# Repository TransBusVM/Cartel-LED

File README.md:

# Cartel-LED

Desarrollo de carteles LED para la empresa TransBus S.R.L.

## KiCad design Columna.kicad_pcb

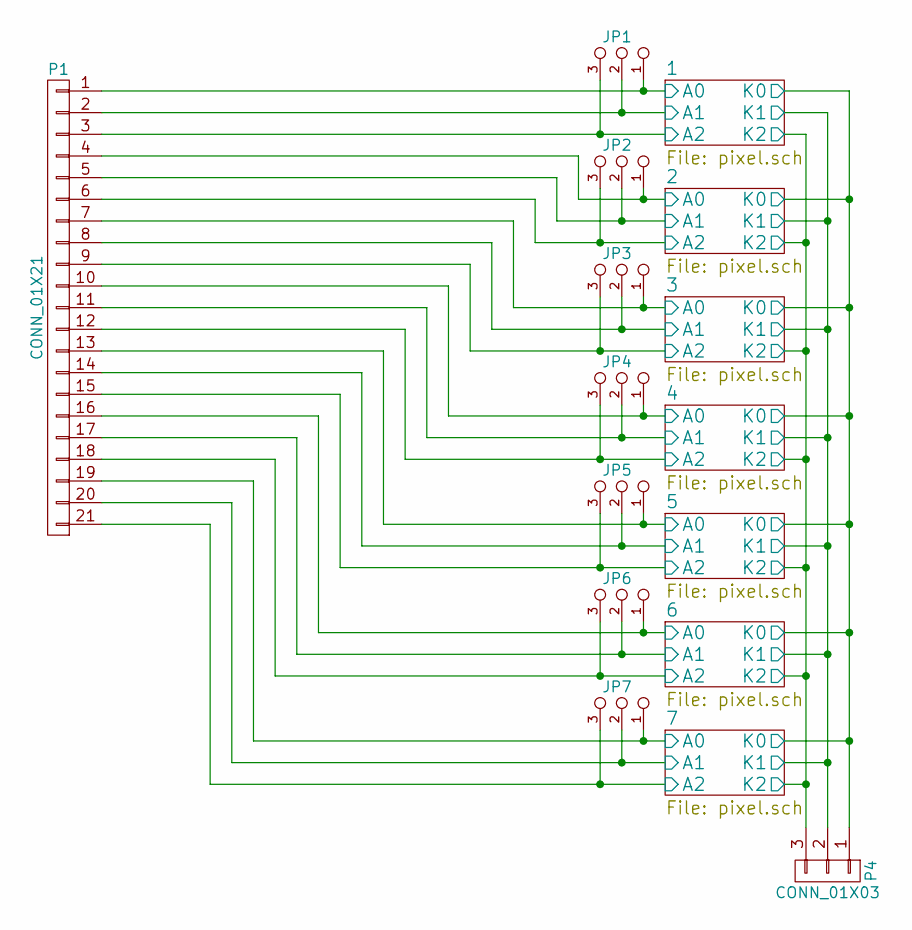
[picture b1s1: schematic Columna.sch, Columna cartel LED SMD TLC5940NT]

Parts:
JP1, JP2, JP3, JP4, JP5, JP6, JP7: JUMPER3_NO; Jumper_3_NO
P1: CONN_01X21; Poste_1x21
P4: CONN_01X03; Poste_1x3

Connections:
/1/A0: JP1.1, P1.1; also elsewhere on the board
/1/A1: JP1.2, P1.2; also elsewhere on the board
/1/A2: JP1.3, P1.3; also elsewhere on the board
/1/K0: P4.1; also elsewhere on the board
/1/K1: P4.2; also elsewhere on the board
/1/K2: P4.3; also elsewhere on the board
/2/A0: JP2.1, P1.4; also elsewhere on the board
/2/A1: JP2.2, P1.5; also elsewhere on the board
/2/A2: JP2.3, P1.6; also elsewhere on the board
/3/A0: JP3.1, P1.7; also elsewhere on the board
/3/A1: JP3.2, P1.8; also elsewhere on the board
/3/A2: JP3.3, P1.9; also elsewhere on the board
/4/A0: JP4.1, P1.10; also elsewhere on the board
/4/A1: JP4.2, P1.11; also elsewhere on the board
/4/A2: JP4.3, P1.12; also elsewhere on the board
/5/A0: JP5.1, P1.13; also elsewhere on the board
/5/A1: JP5.2, P1.14; also elsewhere on the board
/5/A2: JP5.3, P1.15; also elsewhere on the board
/6/A0: JP6.1, P1.16; also elsewhere on the board
/6/A1: JP6.2, P1.17; also elsewhere on the board
/6/A2: JP6.3, P1.18; also elsewhere on the board
/7/A0: JP7.1, P1.19; also elsewhere on the board
/7/A1: JP7.2, P1.20; also elsewhere on the board
/7/A2: JP7.3, P1.21; also elsewhere on the board

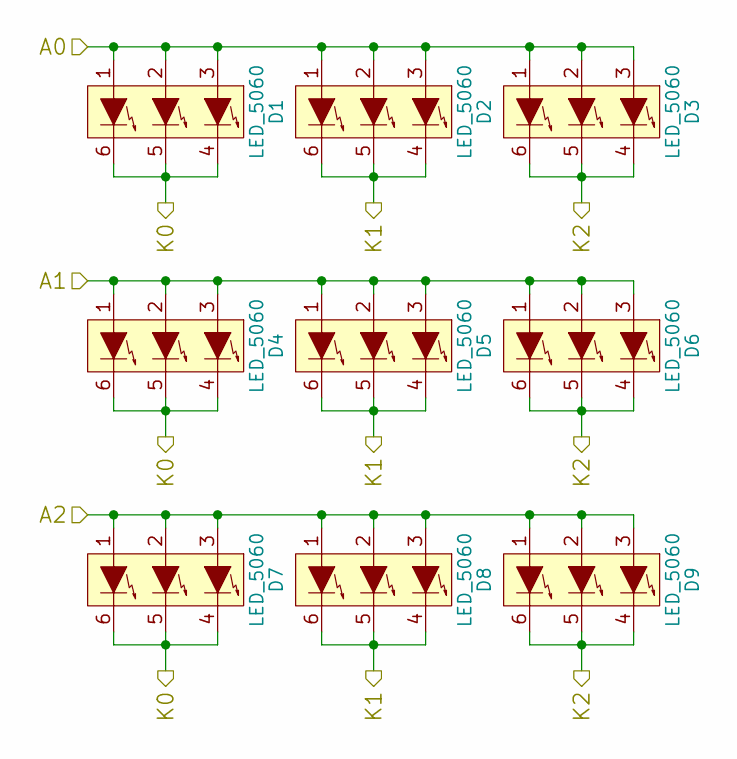
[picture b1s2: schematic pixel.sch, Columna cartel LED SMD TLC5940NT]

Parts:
D1, D2, D3, D4, D5, D6, D7, D8, D9: LED_5060; SMD_5060

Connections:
/1/A0: D1.1, D1.2, D1.3, D2.1, D2.2, D2.3, D3.1, D3.2, D3.3; also elsewhere on the board
/1/A1: D4.1, D4.2, D4.3, D5.1, D5.2, D5.3, D6.1, D6.2, D6.3; also elsewhere on the board
/1/A2: D7.1, D7.2, D7.3, D8.1, D8.2, D8.3, D9.1, D9.2, D9.3; also elsewhere on the board
/1/K0: D1.4, D1.5, D1.6, D4.4, D4.5, D4.6, D7.4, D7.5, D7.6; also elsewhere on the board
/1/K1: D2.4, D2.5, D2.6, D5.4, D5.5, D5.6, D8.4, D8.5, D8.6; also elsewhere on the board
/1/K2: D3.4, D3.5, D3.6, D6.4, D6.5, D6.6, D9.4, D9.5, D9.6; also elsewhere on the board

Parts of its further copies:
D10, D11, D12, D13, D14, D15, D16, D17, D18, D19, D20, D21, D22, D23, D24, D25, D26, D27, D28, D29, D30, D31, D32, D33, D34, D35, D36, D37, D38, D39, D40, D41, D42, D43, D44, D45, D46, D47, D48, D49, D50, D51, D52, D53, D54, D55, D56, D57, D58, D59, D60, D61, D62, D63: LED_5060; SMD_5060

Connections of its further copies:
/1/K0: D10.4, D10.5, D10.6, D13.4, D13.5, D13.6, D16.4, D16.5, D16.6, D19.4, D19.5, D19.6, D22.4, D22.5, D22.6, D25.4, D25.5, D25.6, D28.4, D28.5, D28.6, D31.4, D31.5, D31.6, D34.4, D34.5, D34.6, D37.4, D37.5, D37.6, D40.4, D40.5, D40.6, D43.4, D43.5, D43.6, D46.4, D46.5, D46.6, D49.4, D49.5, D49.6, D52.4, D52.5, D52.6, D55.4, D55.5, D55.6, D58.4, D58.5, D58.6, D61.4, D61.5, D61.6; also elsewhere on the board
/1/K1: D11.4, D11.5, D11.6, D14.4, D14.5, D14.6, D17.4, D17.5, D17.6, D20.4, D20.5, D20.6, D23.4, D23.5, D23.6, D26.4, D26.5, D26.6, D29.4, D29.5, D29.6, D32.4, D32.5, D32.6, D35.4, D35.5, D35.6, D38.4, D38.5, D38.6, D41.4, D41.5, D41.6, D44.4, D44.5, D44.6, D47.4, D47.5, D47.6, D50.4, D50.5, D50.6, D53.4, D53.5, D53.6, D56.4, D56.5, D56.6, D59.4, D59.5, D59.6, D62.4, D62.5, D62.6; also elsewhere on the board
/1/K2: D12.4, D12.5, D12.6, D15.4, D15.5, D15.6, D18.4, D18.5, D18.6, D21.4, D21.5, D21.6, D24.4, D24.5, D24.6, D27.4, D27.5, D27.6, D30.4, D30.5, D30.6, D33.4, D33.5, D33.6, D36.4, D36.5, D36.6, D39.4, D39.5, D39.6, D42.4, D42.5, D42.6, D45.4, D45.5, D45.6, D48.4, D48.5, D48.6, D51.4, D51.5, D51.6, D54.4, D54.5, D54.6, D57.4, D57.5, D57.6, D60.4, D60.5, D60.6, D63.4, D63.5, D63.6; also elsewhere on the board
/2/A0: D10.1, D10.2, D10.3, D11.1, D11.2, D11.3, D12.1, D12.2, D12.3; also elsewhere on the board
/2/A1: D13.1, D13.2, D13.3, D14.1, D14.2, D14.3, D15.1, D15.2, D15.3; also elsewhere on the board
/2/A2: D16.1, D16.2, D16.3, D17.1, D17.2, D17.3, D18.1, D18.2, D18.3; also elsewhere on the board
/3/A0: D19.1, D19.2, D19.3, D20.1, D20.2, D20.3, D21.1, D21.2, D21.3; also elsewhere on the board
/3/A1: D22.1, D22.2, D22.3, D23.1, D23.2, D23.3, D24.1, D24.2, D24.3; also elsewhere on the board
/3/A2: D25.1, D25.2, D25.3, D26.1, D26.2, D26.3, D27.1, D27.2, D27.3; also elsewhere on the board
/4/A0: D28.1, D28.2, D28.3, D29.1, D29.2, D29.3, D30.1, D30.2, D30.3; also elsewhere on the board
/4/A1: D31.1, D31.2, D31.3, D32.1, D32.2, D32.3, D33.1, D33.2, D33.3; also elsewhere on the board
/4/A2: D34.1, D34.2, D34.3, D35.1, D35.2, D35.3, D36.1, D36.2, D36.3; also elsewhere on the board
/5/A0: D37.1, D37.2, D37.3, D38.1, D38.2, D38.3, D39.1, D39.2, D39.3; also elsewhere on the board
/5/A1: D40.1, D40.2, D40.3, D41.1, D41.2, D41.3, D42.1, D42.2, D42.3; also elsewhere on the board
/5/A2: D43.1, D43.2, D43.3, D44.1, D44.2, D44.3, D45.1, D45.2, D45.3; also elsewhere on the board
/6/A0: D46.1, D46.2, D46.3, D47.1, D47.2, D47.3, D48.1, D48.2, D48.3; also elsewhere on the board
/6/A1: D49.1, D49.2, D49.3, D50.1, D50.2, D50.3, D51.1, D51.2, D51.3; also elsewhere on the board
/6/A2: D52.1, D52.2, D52.3, D53.1, D53.2, D53.3, D54.1, D54.2, D54.3; also elsewhere on the board
/7/A0: D55.1, D55.2, D55.3, D56.1, D56.2, D56.3, D57.1, D57.2, D57.3; also elsewhere on the board
/7/A1: D58.1, D58.2, D58.3, D59.1, D59.2, D59.3, D60.1, D60.2, D60.3; also elsewhere on the board
/7/A2: D61.1, D61.2, D61.3, D62.1, D62.2, D62.3, D63.1, D63.2, D63.3; also elsewhere on the board

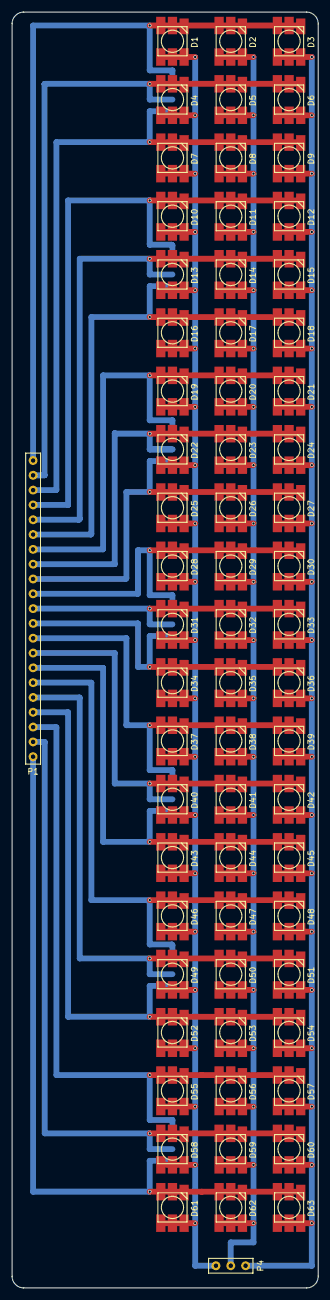
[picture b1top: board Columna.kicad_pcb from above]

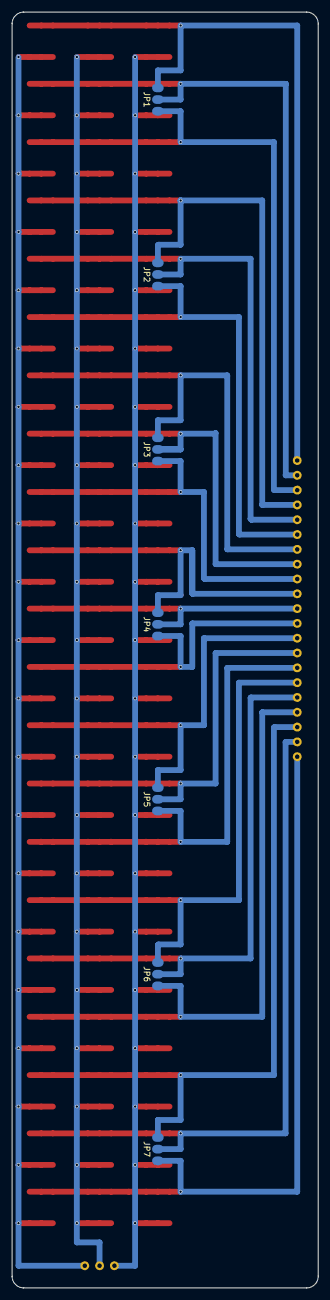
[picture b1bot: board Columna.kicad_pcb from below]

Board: 2 copper layers, 52.5 x 218.8 mm, 72 parts (7 on the bottom side), 24 nets.

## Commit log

2016-09-19 Carga inicial de archivos
    Carga inicial de los archivos que comforman el proyecto
2016-09-20 Se agrega .gitignore
    Se agregan algunas exclusiones al archivo .gitignore
2016-09-20 Modelo 3D de los postes 1x3
2016-09-20 Agrego mas excepciones al .gitignore
2016-09-21 Borro archivos y reacomodo general
    Se borran archivos innecesarios para manejar el proyecto y se reacomodan algunos archivos que pertenecen a las librerías creadas para este cartel
2016-09-24 Logo TransBus
    Se genera y agrega al PCB a modo de prueba el Logo de TransBus en la capa de silkscreen.
2016-10-01 Se quita el Logo, se agregan los archivos para fabricación GERBER
    Se quita el Logo porque se carga demasiado la interfaz gráfica para renderizar el modelo (se podría agregar antes de enviar a fabricar o se podría agregar un logo más liviano), se agregan los archivo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
